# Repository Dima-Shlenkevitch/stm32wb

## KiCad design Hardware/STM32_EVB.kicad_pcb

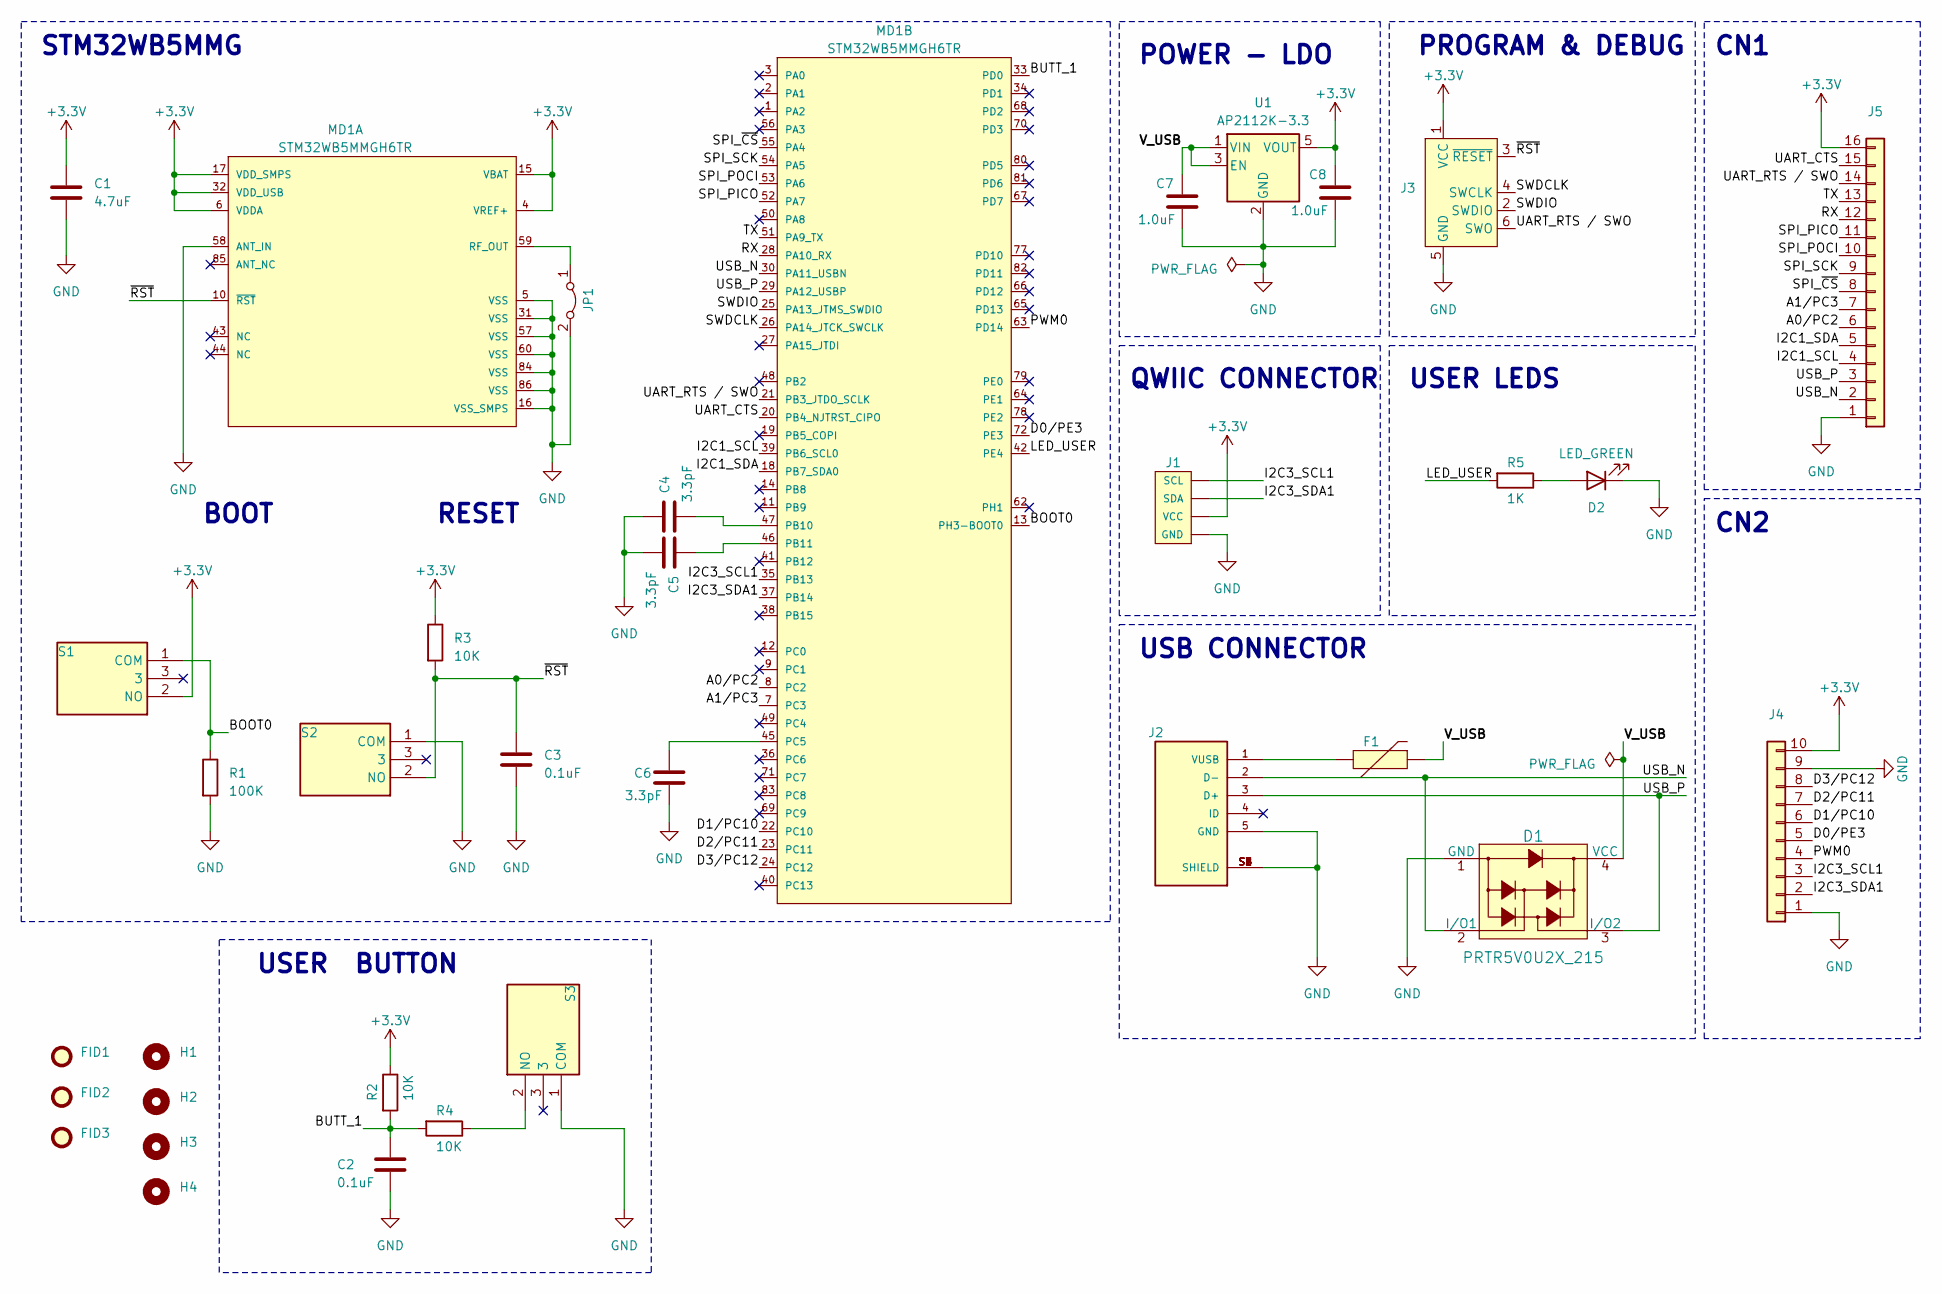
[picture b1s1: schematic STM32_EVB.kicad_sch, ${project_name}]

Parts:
C1: 4.7uF; C_0603_1608Metric_Pad1.08x0.95mm_HandSolder
C2, C3: 0.1uF; C_0603_1608Metric_Pad1.08x0.95mm_HandSolder
C4, C5, C6: 3.3pF; C_0402_1005Metric_Pad0.74x0.62mm_HandSolder
C7, C8: 1.0uF; C_0603_1608Metric_Pad1.08x0.95mm_HandSolder
D1: PRTR5V0U2X_215; TO-253-4; MPN PRTR5V0U2X,215; Digi-Key_PN 1727-3884-1-ND
D2: LED_GREEN; LED_0805_2012Metric_Pad1.15x1.40mm_HandSolder
F1: PPTC_HALF-AMP; Fuse_1206_3216Metric_Pad1.42x1.75mm_HandSolder
FID1, FID2, FID3: Fiducial; Fiducial_0.75mm_Mask1.5mm
H1, H2, H3, H4: MountingHole; MountingHole_2mm
J1: I2C_STANDARDQWIIC; JST_SH_SM04B-SRSS-TB_1x04-1MP_P1.00mm_Horizontal
J2: 10118193-0001LF; USB-micro-AMPHENOL_10118193-0001LF; PARTREV E
J3: Conn_ARM_SWD_TagConnect_TC2030; Tag-Connect_TC2030-IDC-NL_2x03_P1.27mm_Vertical
J4: Conn_01x10; PinSocket_1x10_P2.54mm_Vertical
J5: Conn_01x16; PinHeader_1x16_P2.54mm_Vertical
JP1: Jumper_2_Bridged; SolderJumper-2_P1.3mm_Bridged_RoundedPad1.0x1.5mm
MD1: STM32WB5MMGH6TR; STM32WB5MMGH6TR-MFG; mouser part number 511-STM32WB5MMGH6TR; digikey description ULTRA-LOW-POWER DUAL CORE ARM CO
R1: 100K; R_0603_1608Metric_Pad0.98x0.95mm_HandSolder
R2, R3, R4: 10K; R_0603_1608Metric_Pad0.98x0.95mm_HandSolder
R5: 1K; R_0603_1608Metric_Pad0.98x0.95mm_HandSolder
S1, S2, S3: B3U-1000P-B; Omron_Electronics_Inc-EMC_Div-B3U-1100P-B-MFG; Mouser Part Number 653-B3U-1000P-B
U1: AP2112K-3.3; SOT-23-5

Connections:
+3.3V: C1.1, C8.2, J1.2 (VCC), J3.1 (VCC), J4.10, J5.16, MD1.4 (VREF+), MD1.6 (VDDA), MD1.15 (VBAT), MD1.17 (VDD_SMPS), MD1.32 (VDD_USB), R2.1, R3.1, S1.2 (NO), U1.5 (VOUT)
/A0/PC2: J5.6, MD1.8 (PC2)
/A1/PC3: J5.7, MD1.7 (PC3)
/BOOT0: MD1.13 (PH3-BOOT0), R1.1, S1.1 (COM)
/BUTT_1: C2.2, MD1.33 (PD0), R2.2, R4.2
/D0/PE3: J4.5, MD1.72 (PE3)
/D1/PC10: J4.6, MD1.22 (PC10)
/D2/PC11: J4.7, MD1.23 (PC11)
/D3/PC12: J4.8, MD1.24 (PC12)
/I2C1_SCL: J5.4, MD1.39 (PB6_SCL0)
/I2C1_SDA: J5.5, MD1.18 (PB7_SDA0)
/I2C3_SCL1: J1.4 (SCL), J4.3, MD1.35 (PB13)
/I2C3_SDA1: J1.3 (SDA), J4.2, MD1.37 (PB14)
/LED_USER: MD1.42 (PE4), R5.2
/PWM0: J4.4, MD1.63 (PD14)
/RX: J5.12, MD1.28 (PA10_RX)
/SPI_PICO: J5.11, MD1.52 (PA7)
/SPI_POCI: J5.10, MD1.53 (PA6)
/SPI_SCK: J5.9, MD1.54 (PA5)
/SPI_~CS: J5.8, MD1.55 (PA4)
/SWDCLK: J3.4 (SWCLK), MD1.26 (PA14_JTCK_SWCLK)
/SWDIO: J3.2 (SWDIO), MD1.25 (PA13_JTMS_SWDIO)
/TX: J5.13, MD1.51 (PA9_TX)
/UART_CTS: J5.15, MD1.20 (PB4_NJTRST_CIPO)
/UART_RTS / SWO: J3.6 (SWO), J5.14, MD1.21 (PB3_JTDO_SCLK)
/USB_N: D1.2 (I/O1), J2.2 (D-), J5.2, MD1.30 (PA11_USBN)
/USB_P: D1.3 (I/O2), J2.3 (D+), J5.3, MD1.29 (PA12_USBP)
/V_USB: C7.2, D1.4 (VCC), F1.2, U1.1 (VIN), U1.3 (EN)
/~RST: C3.1, J3.3 (~RESET), MD1.10 (~RST), R3.2, S2.2 (NO)
GND: C1.2, C2.1, C3.2, C4.2, C5.1, C6.1, C7.1, C8.1, D1.1 (GND), D2.1 (K), J1.1 (GND), J2.5 (GND), J2.S1 (SHIELD), J2.S2 (SHIELD), J2.S3 (SHIELD), J2.S4 (SHIELD), J2.S5 (SHIELD), J2.S6 (SHIELD), J3.5 (GND), J4.1, J4.9, J5.1, JP1.2 (B), MD1.5 (VSS), MD1.16 (VSS_SMPS), MD1.31 (VSS), MD1.57 (VSS), MD1.58 (ANT_IN), MD1.60 (VSS), MD1.84 (VSS), MD1.86 (VSS), R1.2, S2.1 (COM), S3.1 (COM), U1.2 (GND)
unnamed: D2.2 (A), R5.1
unnamed: F1.1, J2.1 (VUSB)
unnamed: JP1.1 (A), MD1.59 (RF_OUT)
unnamed: C4.1, MD1.47 (PB10)
unnamed: C5.2, MD1.46 (PB11)
unnamed: C6.2, MD1.45 (PC5)
unnamed: R4.1, S3.2 (NO)

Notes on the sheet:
USB CONNECTOR
POWER - LDO
QWIIC CONNECTOR
RESET
USER LEDS
CN2
USER BUTTON
BOOT
PROGRAM & DEBUG
CN1
STM32WB5MMG

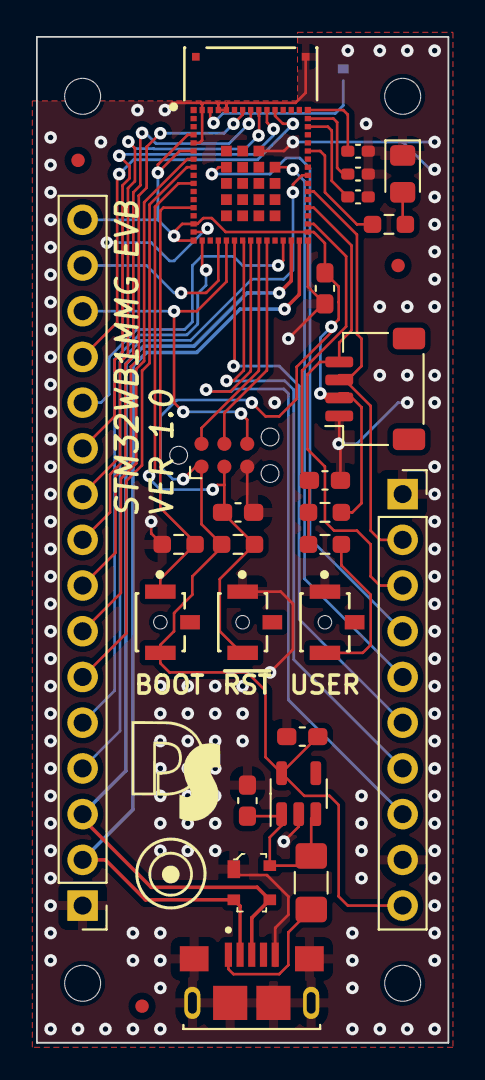
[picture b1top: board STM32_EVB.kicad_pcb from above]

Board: 2 copper layers, 22.9 x 55.9 mm, 34 parts (1 on the bottom side), 37 nets.

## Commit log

2024-05-27 First commit.
2024-05-27 Change picture name.
2024-05-27 Pic name change.
2024-05-27 Pic name changed back.
2024-05-29 .gitignore modified.
2024-05-29 gitignore update.
2024-05-29 modify gitignore
2024-05-29 Check gitignore file
2024-05-29 .gitignore should work now
